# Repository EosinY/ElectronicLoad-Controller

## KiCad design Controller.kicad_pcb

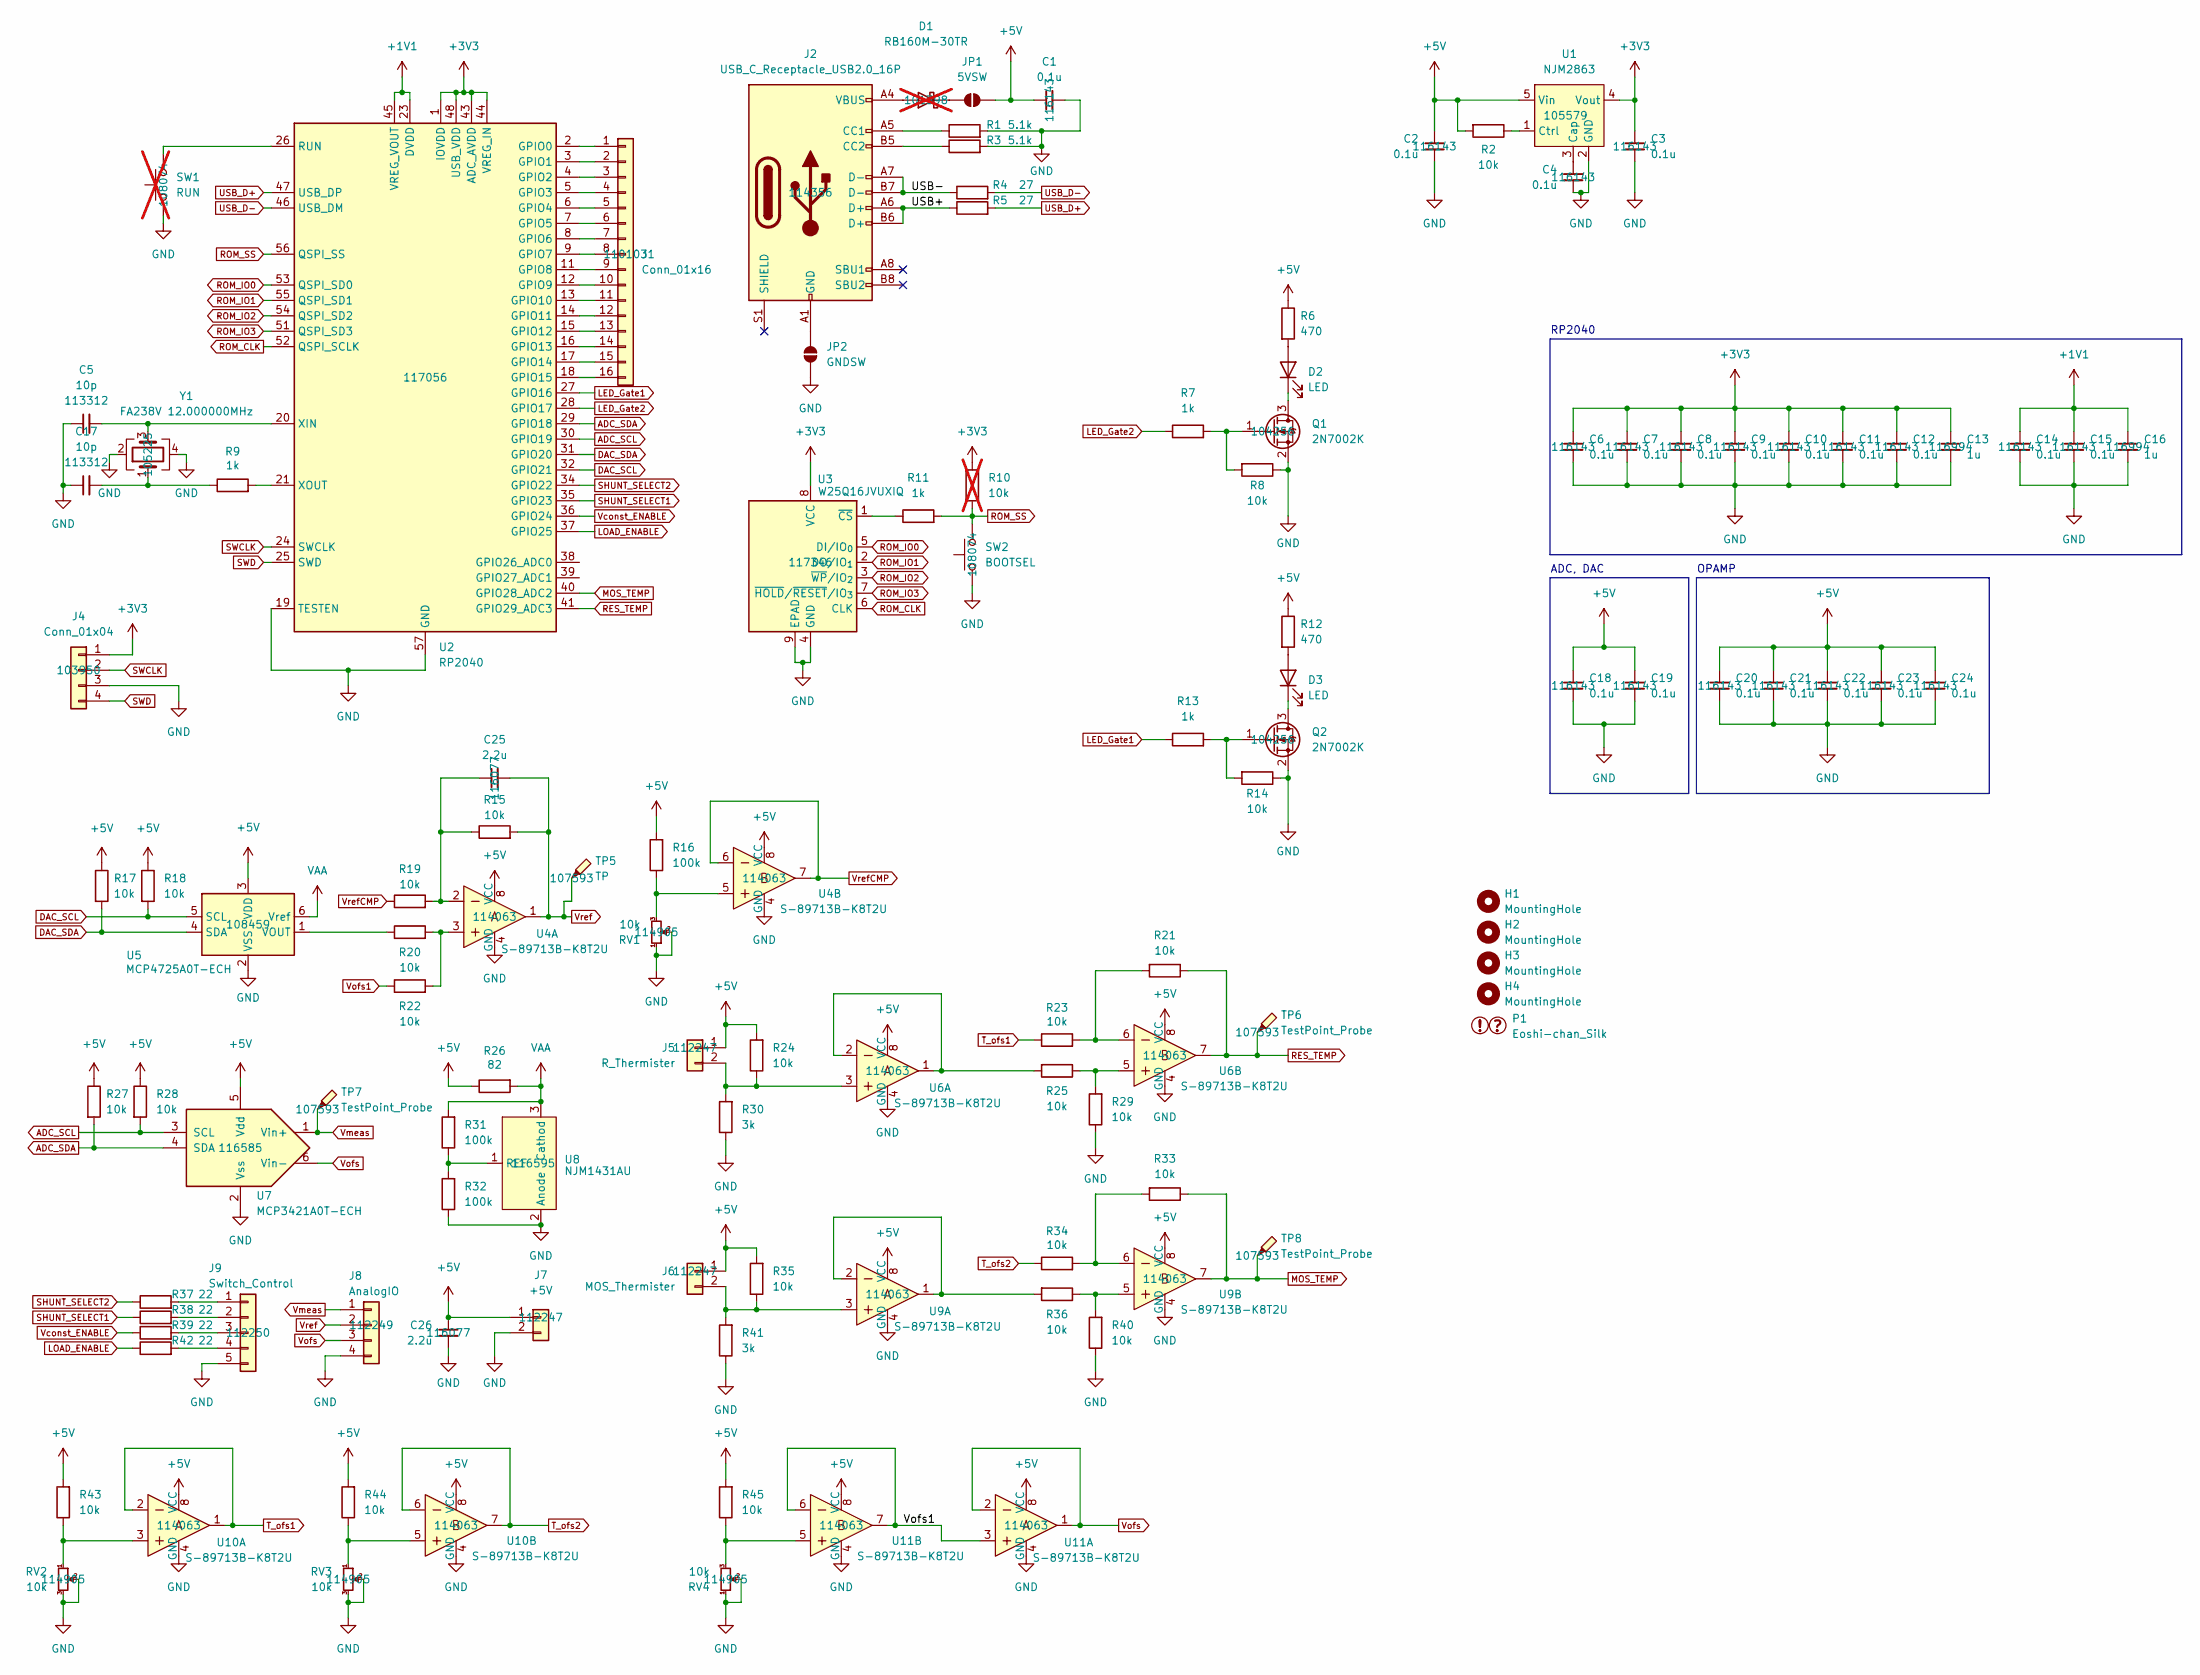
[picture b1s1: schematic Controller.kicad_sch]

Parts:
C1, C2, C3, C4, C6, C7, C8, C9, C10, C11, C12, C14, C15, C18, C19, C20, C21, C22, C23, C24: 0.1u; C_0603_1608Metric
C5, C17: 10p; C_0603_1608Metric
C13, C16: 1u; C_0603_1608Metric
C25, C26: 2.2u; C_0603_1608Metric
D1: RB160M-30TR; D_SOD-123; not fitted
D2, D3: LED; LED_0603_1608Metric
H1, H2, H3, H4: MountingHole; MountingHole_3.2mm_M3
J1: Conn_01x16; PinSocket_1x16_P2.54mm_Vertical
J2: USB_C_Receptacle_USB2.0_16P; USB_C_Receptacle_GCT_USB4105-xx-A_16P_TopMnt_Horizontal
J4: Conn_01x04; PinSocket_1x04_P2.54mm_Vertical
J5: R_Thermister; JST_XH_B2B-XH-A_1x02_P2.50mm_Vertical
J6: MOS_Thermister; JST_XH_B2B-XH-A_1x02_P2.50mm_Vertical
J7: +5V; JST_XH_B2B-XH-A_1x02_P2.50mm_Vertical
J8: AnalogIO; JST_XH_B4B-XH-A_1x04_P2.50mm_Vertical
J9: Switch_Control; JST_XH_B5B-XH-A_1x05_P2.50mm_Vertical
JP1: 5VSW; SolderJumper-2_P1.3mm_Open_TrianglePad1.0x1.5mm
JP2: GNDSW; SolderJumper-2_P1.3mm_Open_TrianglePad1.0x1.5mm
P1: Eoshi-chan_Silk; Eoshi-chan_logo_20x20
Q1, Q2: 2N7002K; SOT-23
R1, R3: 5.1k; R_0603_1608Metric
R2, R8, R14, R15, R17, R18, R19, R20, R21, R22, R23, R24, R25, R27, R28, R29, R33, R34, R35, R36, R40, R43, R44, R45: 10k; R_0603_1608Metric
R4, R5: 27; R_0603_1608Metric
R6, R12: 470; R_0603_1608Metric
R7, R9, R11, R13: 1k; R_0603_1608Metric
R10: 10k; R_0603_1608Metric; not fitted
R16, R31, R32: 100k; R_0603_1608Metric
R26: 82; R_0603_1608Metric
R30, R41: 3k; R_0603_1608Metric
R37, R38, R39, R42: 22; R_0603_1608Metric
RV1, RV2, RV3, RV4: 10k; Potentiometer_Vishay_T73YP_Vertical
SW1: RUN; TVBP06-B043Cx-B; not fitted
SW2: BOOTSEL; TVBP06-B043Cx-B
TP5: TP; TestPoint_THTPad_2.0x2.0mm_Drill1.0mm
TP6, TP7, TP8: TestPoint_Probe; TestPoint_THTPad_2.0x2.0mm_Drill1.0mm
U1: NJM2863; SOT-23-5
U2: RP2040; QFN-56-1EP_7x7mm_P0.4mm_EP3.2x3.2mm
U3: W25Q16JVUXIQ; IC_W25Q16JVUXIQ_TR
U4, U6, U9, U10, U11: S-89713B-K8T2U; MSOP-8_3x3mm_P0.65mm; MPN LM358N; Digi-Key_PN LM358NFS-ND
U5: MCP4725A0T-ECH; SOT-23-6
U7: MCP3421A0T-ECH; SOT-23-6
U8: NJM1431AU; SOT-89-3
Y1: FA238V 12.000000MHz; Crystal_SMD_SeikoEpson_FA238V-4Pin_3.2x2.5mm

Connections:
+1V1: C14.1, C15.1, C16.1, U2.23 (DVDD), U2.45 (VREG_VOUT), U2.50 (DVDD)
+3V3: C3.1, C6.1, C7.1, C8.1, C9.1, C10.1, C11.1, C12.1, C13.1, J4.1, R10.2, U1.4 (Vout), U2.1 (IOVDD), U2.10 (IOVDD), U2.22 (IOVDD), U2.33 (IOVDD), U2.42 (IOVDD), U2.43 (ADC_AVDD), U2.44 (VREG_IN), U2.48 (USB_VDD), U2.49 (IOVDD), U3.8 (VCC)
+5V: C1.1, C2.1, C18.1, C19.1, C20.1, C21.1, C22.1, C23.1, C24.1, C26.1, J5.1, J6.1, J7.1, JP1.2 (B), R2.2, R6.1, R12.1, R16.2, R17.1, R18.1, R24.2, R26.1, R27.1, R28.1, R35.2, R43.2, R44.2, R45.2, U1.5 (Vin), U4.8 (VCC), U5.3 (VDD), U6.8 (VCC), U7.5 (Vdd), U9.8 (VCC), U10.8 (VCC), U11.8 (VCC)
/USB+: J2.A6 (D+), J2.B6 (D+), R5.1
/USB-: J2.A7 (D-), J2.B7 (D-), R4.1
ADC_SCL: R28.2, U2.30 (GPIO19), U7.3 (SCL)
ADC_SDA: R27.2, U2.29 (GPIO18), U7.4 (SDA)
DAC_SCL: R18.2, U2.32 (GPIO21), U5.5 (SCL)
DAC_SDA: R17.2, U2.31 (GPIO20), U5.4 (SDA)
GND: C1.2, C2.2, C3.2, C4.2, C5.1, C6.2, C7.2, C8.2, C9.2, C10.2, C11.2, C12.2, C13.2, C14.2, C15.2, C16.2, C17.1, C18.2, C19.2, C20.2, C21.2, C22.2, C23.2, C24.2, C26.2, J4.3, J7.2, J8.4, J9.5, JP2.1 (A), Q1.2 (S), Q2.2 (S), R1.2, R3.2, R8.1, R14.1, R29.1, R30.1, R32.1, R40.1, R41.1, RV1.1, RV1.2, RV2.2, RV2.3, RV3.2, RV3.3, RV4.1, RV4.2, SW1.1, SW2.1, U1.2 (GND), U2.19 (TESTEN), U2.57 (GND), U3.4 (GND), U3.9 (EPAD), U4.4 (GND), U5.2 (VSS), U6.4 (GND), U7.2 (Vss), U8.2 (Anode), U9.4 (GND), U10.4 (GND), U11.4 (GND), Y1.2, Y1.4
LED_Gate1: R13.1, U2.27 (GPIO16)
LED_Gate2: R7.1, U2.28 (GPIO17)
LOAD_ENABLE: R42.1, U2.37 (GPIO25)
MOS_TEMP: R33.1, TP8.1, U2.40 (GPIO28_ADC2), U9.7
unnamed: C17.2, R9.1, Y1.1
unnamed: C25.1, R15.1, R19.2, U4.2
unnamed: D1.2 (A), J2.A4 (VBUS), J2.A9 (VBUS), J2.B4 (VBUS), J2.B9 (VBUS)
unnamed: D1.1 (K), JP1.1 (A)
unnamed: D2.2 (A), R6.2
unnamed: D2.1 (K), Q1.3 (D)
unnamed: D3.2 (A), R12.2
unnamed: D3.1 (K), Q2.3 (D)
unnamed: J1.1, U2.2 (GPIO0)
unnamed: J1.2, U2.3 (GPIO1)
unnamed: J1.3, U2.4 (GPIO2)
unnamed: J1.4, U2.5 (GPIO3)
unnamed: J1.5, U2.6 (GPIO4)
unnamed: J1.6, U2.7 (GPIO5)
unnamed: J1.7, U2.8 (GPIO6)
unnamed: J1.8, U2.9 (GPIO7)
unnamed: J1.9, U2.11 (GPIO8)
unnamed: J1.10, U2.12 (GPIO9)
unnamed: J1.11, U2.13 (GPIO10)
unnamed: J1.12, U2.14 (GPIO11)
unnamed: J1.13, U2.15 (GPIO12)
unnamed: J1.14, U2.16 (GPIO13)
unnamed: J1.15, U2.17 (GPIO14)
unnamed: J1.16, U2.18 (GPIO15)
unnamed: J2.A5 (CC1), R1.1
unnamed: J2.B5 (CC2), R3.1
unnamed: J5.2, R24.1, R30.2, U6.3
unnamed: J6.2, R35.1, R41.2, U9.3
unnamed: J9.1, R37.2
unnamed: J9.2, R38.2
unnamed: J9.3, R39.2
unnamed: J9.4, R42.2
unnamed: J2.A1 (GND), J2.A12 (GND), J2.B1 (GND), J2.B12 (GND), JP2.2 (B)
unnamed: Q1.1 (G), R7.2, R8.2
unnamed: Q2.1 (G), R13.2, R14.2
unnamed: R16.1, RV1.3, U4.5
unnamed: R20.2, R22.2, U4.3
unnamed: R21.2, R23.2, U6.6
unnamed: R25.1, R29.2, U6.5
unnamed: R25.2, U6.1, U6.2
unnamed: R33.2, R34.2, U9.6
unnamed: R36.1, R40.2, U9.5
unnamed: R36.2, U9.1, U9.2
unnamed: R43.1, RV2.1, U10.3
unnamed: R44.1, RV3.1, U10.5
unnamed: R45.1, RV4.3, U11.5
unnamed: C4.1, U1.3 (Cap)
unnamed: R2.1, U1.1 (Ctrl)
unnamed: SW1.2, U2.26 (RUN)
unnamed: C5.2, U2.20 (XIN), Y1.3
unnamed: R9.2, U2.21 (XOUT)
unnamed: R11.1, U3.1 (~CS)
unnamed: R20.1, U5.1 (VOUT)
unnamed: R31.1, R32.2, U8.1 (REF)
RES_TEMP: R21.1, TP6.1, U2.41 (GPIO29_ADC3), U6.7
ROM_CLK: U2.52 (QSPI_SCLK), U3.6 (CLK)
ROM_IO0: U2.53 (QSPI_SD0), U3.5 (DI/IO_{0})
ROM_IO1: U2.55 (QSPI_SD1), U3.2 (DO/IO_{1})
ROM_IO2: U2.54 (QSPI_SD2), U3.3 (~WP/IO_{2})
ROM_IO3: U2.51 (QSPI_SD3), U3.7 (~HOLD/~RESET/IO_{3})
ROM_SS: R10.1, R11.2, SW2.2, U2.56 (QSPI_SS)
SHUNT_SELECT1: R38.1, U2.35 (GPIO23)
SHUNT_SELECT2: R37.1, U2.34 (GPIO22)
SWCLK: J4.2, U2.24 (SWCLK)
SWD: J4.4, U2.25 (SWD)
T_ofs1: R23.1, U10.1, U10.2
T_ofs2: R34.1, U10.6, U10.7
USB_D+: R5.2, U2.47 (USB_DP)
USB_D-: R4.2, U2.46 (USB_DM)
VAA: R26.2, R31.2, U5.6 (Vref), U8.3 (Cathod)
Vconst_ENABLE: R39.1, U2.36 (GPIO24)
Vmeas: J8.1, TP7.1, U7.1 (Vin+)
Vofs: J8.3, U7.6 (Vin-), U11.1, U11.2
Vofs1: R22.1, U11.3, U11.6, U11.7
Vref: C25.2, J8.2, R15.2, TP5.1, U4.1
VrefCMP: R19.1, U4.6, U4.7

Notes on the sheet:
OPAMP
RP2040
ADC, DAC

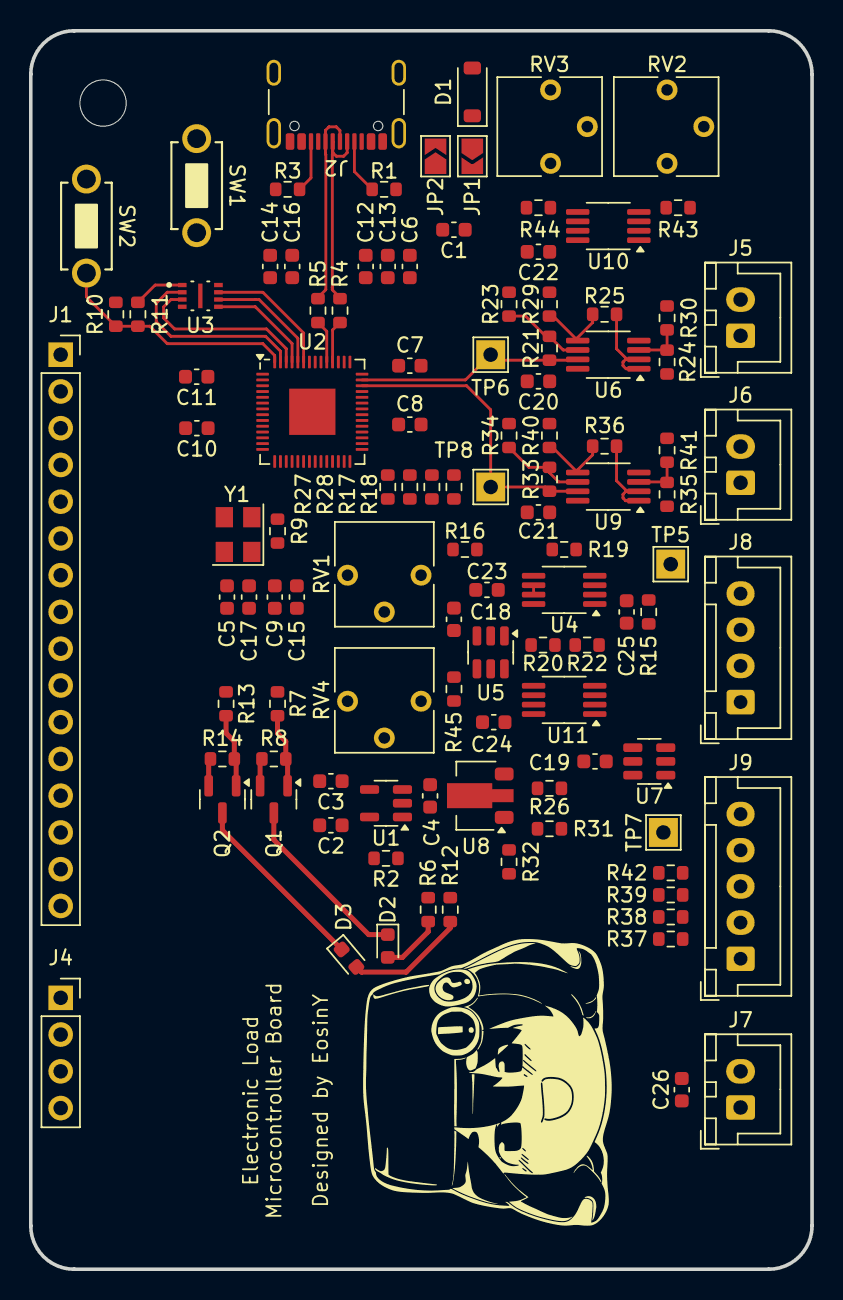
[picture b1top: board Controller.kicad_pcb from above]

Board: 4 copper layers, 54.0 x 85.6 mm, 113 parts (0 on the bottom side), 90 nets.

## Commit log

2025-03-13 First
2025-03-24 Add BOM
2025-03-24 aligned BOM csv
